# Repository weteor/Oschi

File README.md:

### oschi

a orthogonal le chiffre-esk keyboard with hummingbird style alpha options

## Features

- MX-Hotswap sockets
- CH552T Controller (w/ FAK firmware)
- gerber and case files are supplied (kicad files, stl as well as cadquery files)
- completely open source, permissive license ([CERN-OHL-P](https://cern-ohl.web.cern.ch/home))

##### layout options

make sure to grab the right combinations of plate and case top.

## Want one?

All production files you need to build your own board can be found [here](./prod/).

Apart from the pcb and optionally a case you need:

- 38 hotswap sockets

- 38 diodes (1N4148 int SOT-123)

- 38 of your favourite switches

- 1x CH552T (TSSOP-20)

- 1x USBLC6-2SC6 (SOT-23-6)

- 1x 10kOhm resistor (SMD 0603)

- 2x 5.1kOhm resistors (SMD 0603)

- 2x 100nF capacitors (SMD 0603)

- 1x USB Connector C-Type, 12 pin/16pin

### firmware

Config for FAK can be found [here](https://github.com/weteor/fak-config/tree/main/keyboards/oschi). Please also see [FAK-Firmware site](https://github.com/semickolon/fak) for more information

Bootloader should be available on plugin until firmware is written. After that either use the firmware BOOT to go into bootloader, or hold the boot button on the pcb pressed while pluggin in the usb cable.

### the rest

Everything in this repository is free to use however you might see fit. If you want to support me and my projects, please consider linking back to this repository if you build/change/use anything.

If you would like to send me a tip, you could do it [here](https://ko-fi.com/weteor) (Please don't feel like you have to).

### more pictures

---

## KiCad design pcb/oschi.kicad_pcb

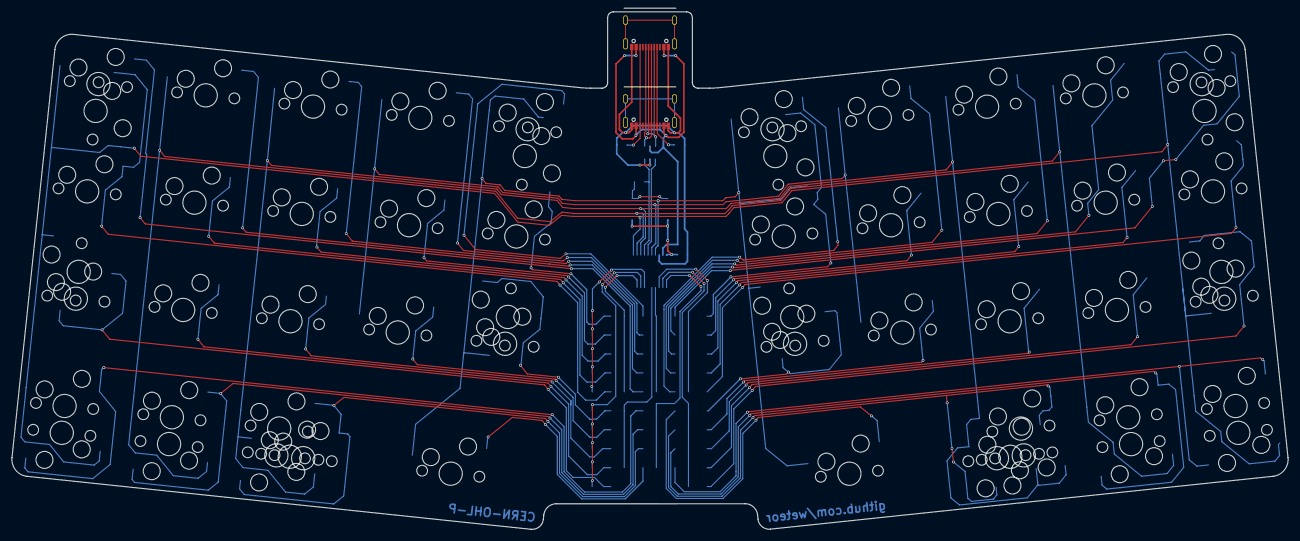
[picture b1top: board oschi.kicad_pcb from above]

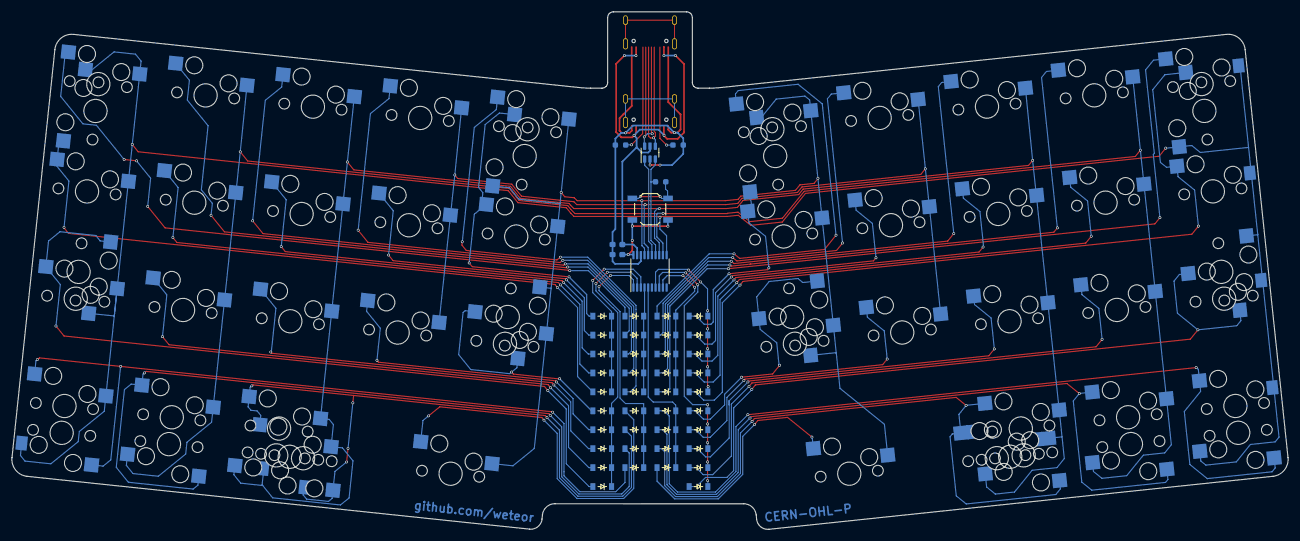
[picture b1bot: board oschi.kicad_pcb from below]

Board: 2 copper layers, 225.3 x 91.4 mm, 104 parts (46 on the bottom side), 61 nets.

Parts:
C1, C2: 100nF; C_0603_HandSolder
D1, D2, D3, D4, D5, D6, D7, D8, D9, D10, D11, D12, D13, D14, D15, D16, D17, D18, D19, D20, D21, D22, D23, D24, D25, D26, D27, D28, D29, D30, D31, D32, D33, D34, D35, D36, D37, D38: D; D_SOD-123
J1, J2: USB_C_Receptacle_USB2.0; USB C-31-M-12
R1, R2: 5.1k; R_0603_HandSolder
R3: 10k; R_0603_HandSolder
SW1, SW2, SW3, SW4, SW5, SW6, SW7, SW8, SW9, SW10, SW11, SW12, SW13, SW14, SW15, SW17, SW18, SW19, SW20, SW21, SW22, SW24, SW25, SW26, SW29, SW30, SW31, SW32, SW33, SW34, SW35, SW36, SW37, SW39, SW40, SW41, SW42, SW43, SW44, SW45, SW46, SW47, SW56, SW57: SW_Push; CherryMX_Hotswap_3d
SW16, SW38: SW_Push; CherryMX_Hotswap_1.25u
SW23, SW27: SW_Push; CherryMX_Hotswap_1.75u_3d
SW28: BOOT; SW_SPST_TL3342
SW48, SW49, SW50, SW51, SW52, SW53, SW54, SW55: SW_Push; CherryMX_Hotswap_1.5u
U1: USBLC6-2SC6; SOT-23-6
U2: TSSOP-20_4.4x6.5mm_P0.65mm

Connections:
+3.3V: C1.1, SW28.2, U2.20 (V33)
BOOT: R3.2, SW28.1
CC1: J1.A5 (CC1), J2.A5 (CC1), R1.1
CC2: J1.B5 (CC2), J2.B5 (CC2), R2.1
Col_1: SW1.1, SW2.1, SW3.1, SW4.1, SW44.1, SW45.1, SW46.1, SW47.1, SW52.2, SW53.2, SW54.1, SW55.1, SW56.1, SW57.1, U2.11 (P3.3)
Col_2: SW5.1, SW6.1, SW7.1, SW8.1, SW9.1, SW39.1, SW40.1, SW41.1, SW42.1, SW43.1, U2.12 (P3.4)
Col_3: SW10.1, SW11.1, SW12.1, SW13.1, SW14.1, SW15.1, SW16.1, SW32.1, SW33.1, SW34.1, SW35.1, SW36.1, SW37.1, SW38.1, U2.13 (P3.5)
Col_4: SW17.1, SW18.1, SW19.1, SW29.1, SW30.1, SW31.1, U2.16 (P1.3)
Col_5: SW20.1, SW21.1, SW22.1, SW23.1, SW24.1, SW25.1, SW26.1, SW27.1, SW48.1, SW49.1, SW50.2, SW51.2, U2.17 (P1.2)
GND: C1.2, C2.2, J1.A1 (GND), J1.A12 (GND), J1.B1 (GND), J1.B12 (GND), J2.A1 (GND), J2.A12 (GND), J2.B1 (GND), J2.B12 (GND), R1.2, R2.2, U1.2 (GND), U2.18 (GND)
unnamed: D1.2 (A), SW1.2, SW52.1
unnamed: D2.2 (A), SW2.2, SW53.1
unnamed: D3.2 (A), SW3.2, SW4.2
unnamed: D4.2 (A), SW5.2
unnamed: D5.2 (A), SW6.2
unnamed: D6.2 (A), SW7.2
unnamed: D7.2 (A), SW8.2, SW9.2
unnamed: D8.2 (A), SW10.2
unnamed: D9.2 (A), SW11.2
unnamed: D10.2 (A), SW12.2
unnamed: D11.2 (A), SW13.2, SW14.2, SW15.2, SW16.2
unnamed: D12.2 (A), SW17.2
unnamed: D13.2 (A), SW18.2
unnamed: D14.2 (A), SW19.2
unnamed: D15.2 (A), SW20.2
unnamed: D16.2 (A), SW21.2, SW48.2
unnamed: D17.2 (A), SW22.2, SW49.2
unnamed: D18.2 (A), SW23.2
unnamed: D19.2 (A), SW24.2
unnamed: D20.2 (A), SW25.2, SW50.1
unnamed: D21.2 (A), SW26.2, SW51.1
unnamed: D22.2 (A), SW27.2
unnamed: D23.2 (A), SW29.2
unnamed: D24.2 (A), SW30.2
unnamed: D25.2 (A), SW31.2
unnamed: D26.2 (A), SW32.2
unnamed: D27.2 (A), SW33.2
unnamed: D28.2 (A), SW34.2
unnamed: D29.2 (A), SW35.2, SW36.2, SW37.2, SW38.2
unnamed: D30.2 (A), SW39.2
unnamed: D31.2 (A), SW40.2
unnamed: D32.2 (A), SW41.2
unnamed: D33.2 (A), SW42.2, SW43.2
unnamed: D34.2 (A), SW44.2, SW54.2
unnamed: D35.2 (A), SW45.2, SW55.2
unnamed: D36.2 (A), SW46.2, SW47.2
unnamed: D37.2 (A), SW56.2
unnamed: D38.2 (A), SW57.2
PORT+: J1.A6 (D+), J1.B6 (D+), J2.A6 (D+), J2.B6 (D+), U1.4 (I/O2)
PORT-: J1.A7 (D-), J1.B7 (D-), J2.A7 (D-), J2.B7 (D-), U1.6 (I/O1)
Row_1: D4.1 (K), D8.1 (K), D12.1 (K), D15.1 (K), D37.1 (K), U2.9 (P3.1)
Row_2: D1.1 (K), D5.1 (K), D9.1 (K), D13.1 (K), D16.1 (K), U2.7 (P1.0)
Row_3: D2.1 (K), D6.1 (K), D10.1 (K), D14.1 (K), D17.1 (K), U2.8 (P1.1)
Row_4: D3.1 (K), D7.1 (K), D11.1 (K), D18.1 (K), U2.5 (P1.7)
Row_5: D19.1 (K), D23.1 (K), D26.1 (K), D30.1 (K), D38.1 (K), U2.4 (P1.6)
Row_6: D20.1 (K), D24.1 (K), D27.1 (K), D31.1 (K), D34.1 (K), U2.3 (P1.5)
Row_7: D21.1 (K), D25.1 (K), D28.1 (K), D32.1 (K), D35.1 (K), U2.2 (P1.4)
Row_8: D22.1 (K), D29.1 (K), D33.1 (K), D36.1 (K), U2.1 (P3.2)
UDM: U1.1 (I/O1), U2.15 (P3.7)
UDP: R3.1, U1.3 (I/O2), U2.14 (P3.6)
VBUS: C2.1, J1.A4 (VBUS), J1.A9 (VBUS), J1.B4 (VBUS), J1.B9 (VBUS), J2.A4 (VBUS), J2.A9 (VBUS), J2.B4 (VBUS), J2.B9 (VBUS), U1.5 (VBUS), U2.19 (VCC)

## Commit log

2024-07-23 add pcb
2024-07-23 add case
2024-07-23 add prod data
2024-07-23 add readme, licence and img
